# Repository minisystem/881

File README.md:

SYSTEM80 881
======================================

Trigger expander module for 880

Hardware design by Minisystem: info@system80.net

LICENSE
=======
cc by-nc-sa
https://creativecommons.org/licenses/by-nc-sa/4.0/

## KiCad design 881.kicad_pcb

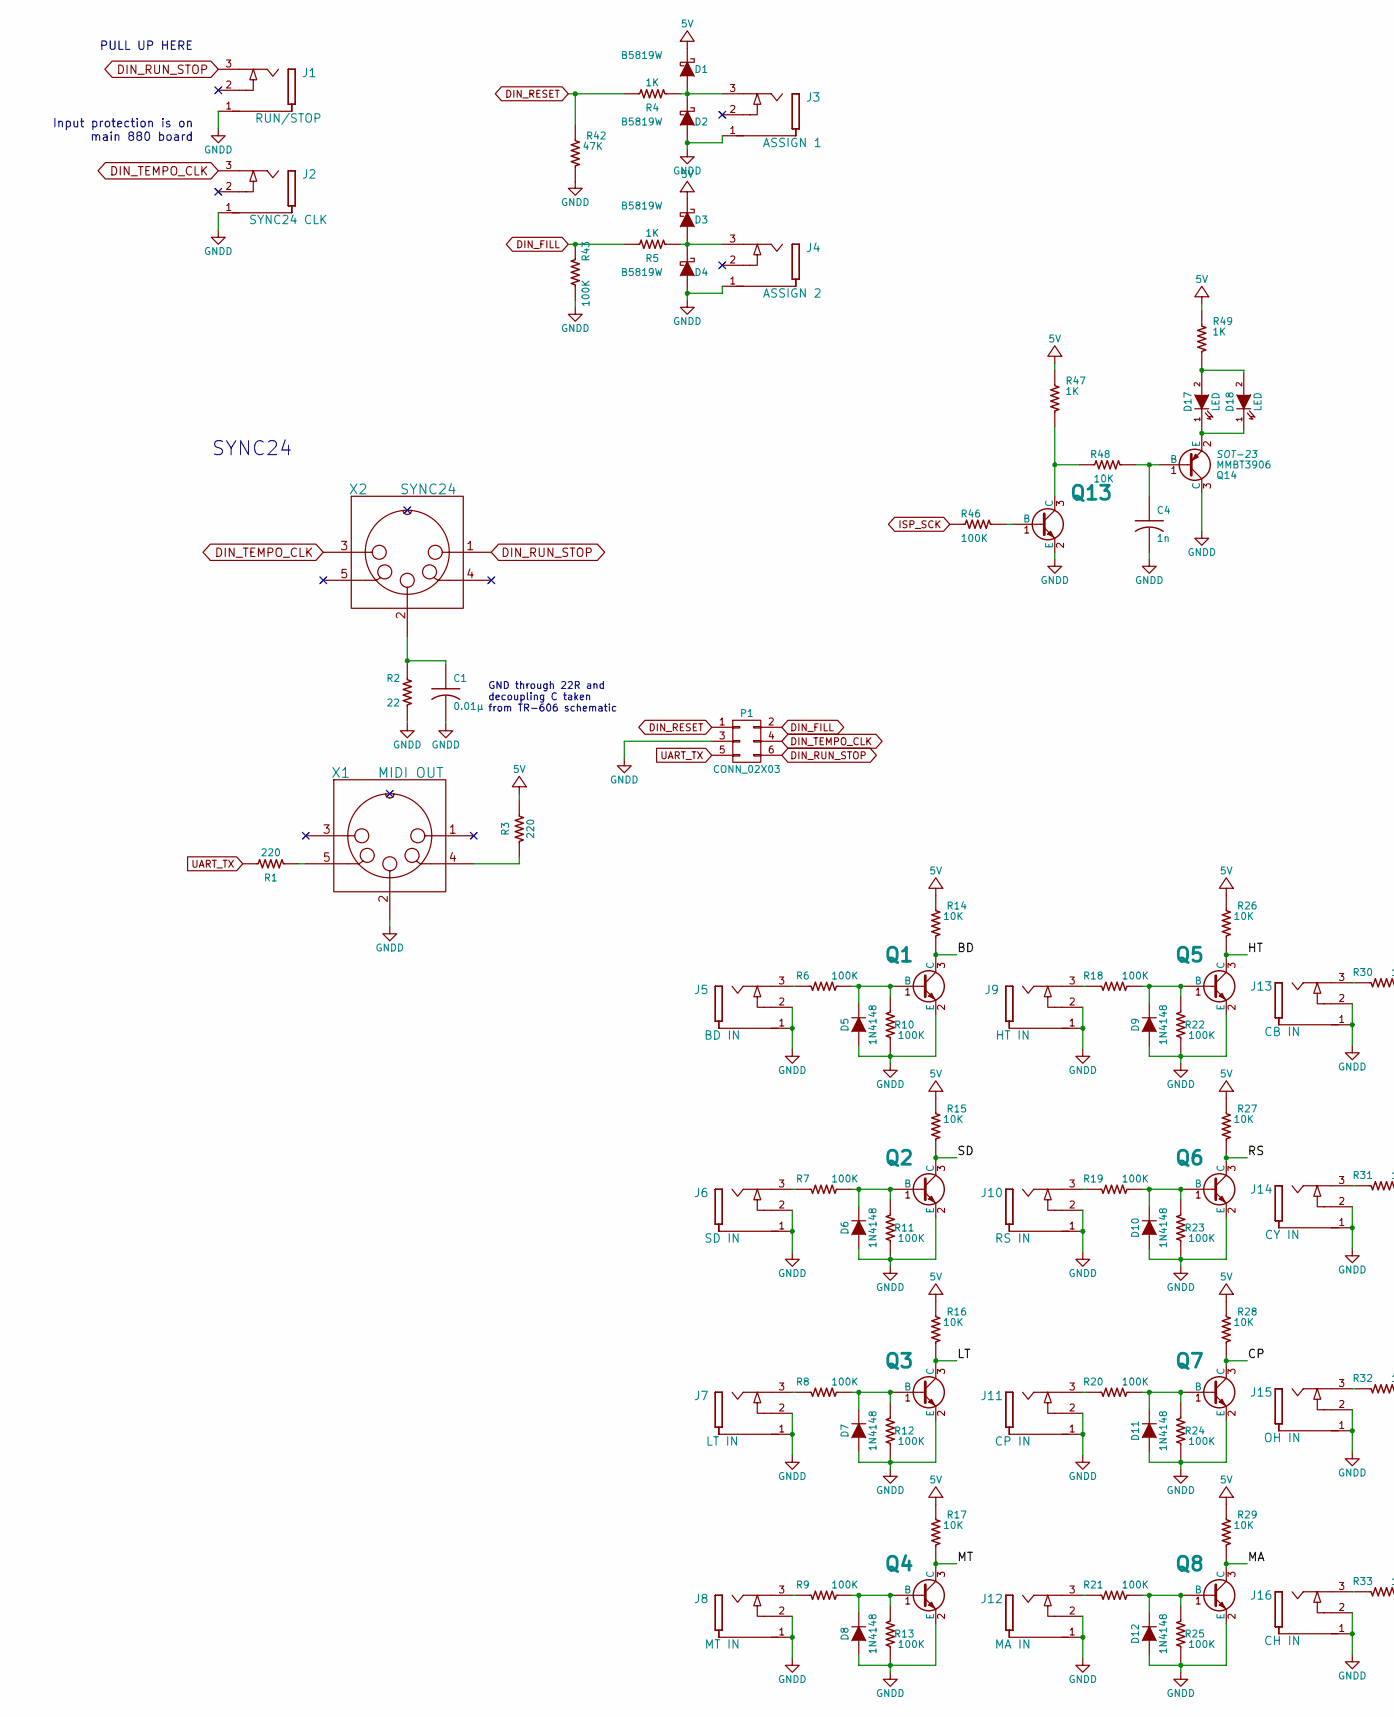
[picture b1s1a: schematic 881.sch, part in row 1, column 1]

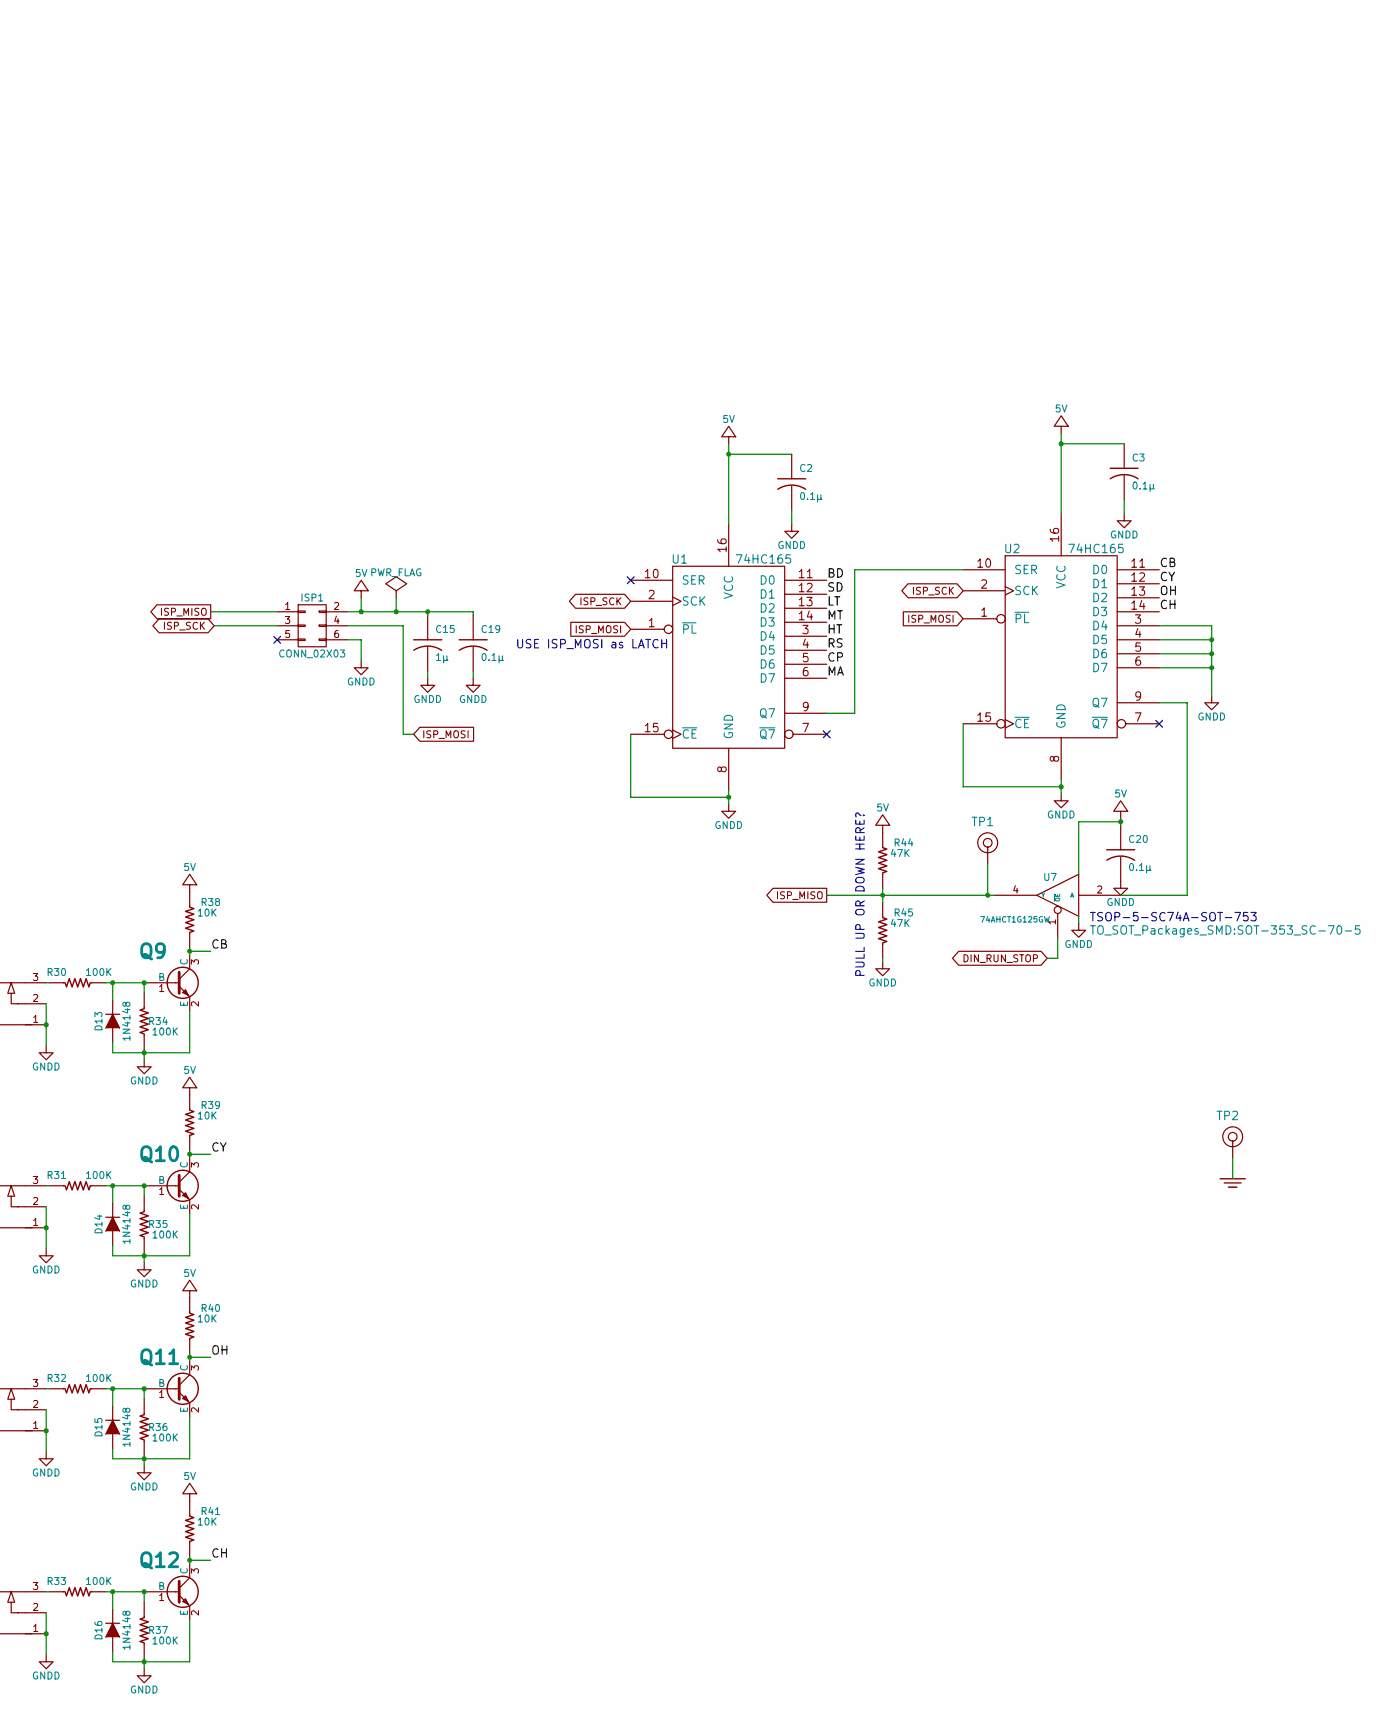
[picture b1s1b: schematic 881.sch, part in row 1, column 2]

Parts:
C1: 0.01µ; SM0603-C-MURATA
C2, C3, C19, C20: 0.1µ; SM0603-C-MURATA
C4: 1n; SM0603-C-MURATA
C15: 1µ; C_0805
D1: B5819W; D_SOD-123; JLC C8598
D2, D3, D4: B5819W; D_SOD-123
D5: 1N4148; D_SOD-323F; JLC C2128
D6, D7, D8, D9, D10, D11, D12, D13, D14, D15, D16: 1N4148; SOD323-C1A2
D17: LED; LED_0805; JLC C84256
D18: LED; LED_D3.0mm
ISP1: CONN_02X03; vasch_strip_3x2
J1: RUN/STOP; PJ-301B-JACK-SLOTS
J2: SYNC24 CLK; PJ-301B-JACK-SLOTS
J3: ASSIGN 1; PJ-301B-JACK-SLOTS
J4: ASSIGN 2; PJ-301B-JACK-SLOTS
J5: BD IN; PJ-301B-JACK-SLOTS
J6: SD IN; PJ-301B-JACK-SLOTS
J7: LT IN; PJ-301B-JACK-SLOTS
J8: MT IN; PJ-301B-JACK-SLOTS
J9: HT IN; PJ-301B-JACK-SLOTS
J10: RS IN; PJ-301B-JACK-SLOTS
J11: CP IN; PJ-301B-JACK-SLOTS
J12: MA IN; PJ-301B-JACK-SLOTS
J13: CB IN; PJ-301B-JACK-SLOTS
J14: CY IN; PJ-301B-JACK-SLOTS
J15: OH IN; PJ-301B-JACK-SLOTS
J16: CH IN; PJ-301B-JACK-SLOTS
P1: CONN_02X03; vasch_strip_4x2
Q1, Q2, Q3, Q4, Q5, Q6, Q7, Q8, Q9, Q10, Q11, Q12, Q13: MMBT3904; SOT23-132-JRL
Q14: MMBT3906; SOT-23
R1, R3: 220; SM0603-R-YAGEO
R2: 22; SM0603-R-YAGEO
R4, R5, R47, R49: 1K; SM0603-R-YAGEO
R6, R7, R8, R9, R10, R11, R12, R13, R18, R19, R20, R21, R22, R23, R24, R25, R30, R31, R32, R33, R34, R35, R36, R37, R43, R46: 100K; SM0603-R-YAGEO
R14, R15, R16, R17, R26, R27, R28, R29, R38, R39, R40, R41, R48: 10K; SM0603-R-YAGEO
R42, R44, R45: 47K; SM0603-R-YAGEO
TP1, TP2: CONN_1; TEST_POINT_LOOP_4592
U1, U2: 74HC165; SOIC-16_3.9x9.9mm_Pitch1.27mm; JLC C5613
U7: 74AHCT1G125GW; SOT-353_SC-70-5; JLC C12495
X1: MIDI OUT; SD-50BV-5DIN
X2: SYNC24; SD-50BV-5DIN

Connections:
+5V: C2.1, C3.1, C15.1, C19.1, C20.1, D1.1 (K), D3.1 (K), ISP1.2, R3.2, R14.1, R15.1, R16.1, R17.1, R26.1, R27.1, R28.1, R29.1, R38.1, R39.1, R40.1, R41.1, R44.1, R47.1, R49.1, U1.16 (VCC), U2.16 (VCC), U7.5 (VCC)
/BD: Q1.3 (C), R14.2, U1.11 (D0)
/CB: Q9.3 (C), R38.2, U2.11 (D0)
/CH: Q12.3 (C), R41.2, U2.14 (D3)
/CP: Q7.3 (C), R28.2, U1.5 (D6)
/CY: Q10.3 (C), R39.2, U2.12 (D1)
/HT: Q5.3 (C), R26.2, U1.3 (D4)
/LT: Q3.3 (C), R16.2, U1.13 (D2)
/MA: Q8.3 (C), R29.2, U1.6 (D7)
/MT: Q4.3 (C), R17.2, U1.14 (D3)
/OH: Q11.3 (C), R40.2, U2.13 (D2)
/RS: Q6.3 (C), R27.2, U1.4 (D5)
/SD: Q2.3 (C), R15.2, U1.12 (D1)
DIN_FILL: P1.2, R5.2, R43.1
DIN_RESET: P1.1, R4.2, R42.1
DIN_RUN_STOP: J1.3, P1.6, U7.1 (~OE), X2.1
DIN_TEMPO_CLK: J2.3, P1.4, X2.3
GNDD: C1.2, C2.2, C3.2, C4.2, C15.2, C19.2, C20.2, D2.2 (A), D4.2 (A), D5.2 (A), D6.2 (A), D7.2 (A), D8.2 (A), D9.2 (A), D10.2 (A), D11.2 (A), D12.2 (A), D13.2 (A), D14.2 (A), D15.2 (A), D16.2 (A), ISP1.6, J1.1, J2.1, J3.1, J4.1, J5.1, J5.2, J6.1, J6.2, J7.1, J7.2, J8.1, J8.2, J9.1, J9.2, J10.1, J10.2, J11.1, J11.2, J12.1, J12.2, J13.1, J13.2, J14.1, J14.2, J15.1, J15.2, J16.1, J16.2, P1.3, Q1.2 (E), Q2.2 (E), Q3.2 (E), Q4.2 (E), Q5.2 (E), Q6.2 (E), Q7.2 (E), Q8.2 (E), Q9.2 (E), Q10.2 (E), Q11.2 (E), Q12.2 (E), Q13.2 (E), Q14.3 (C), R2.1, R10.2, R11.2, R12.2, R13.2, R22.2, R23.2, R24.2, R25.2, R34.2, R35.2, R36.2, R37.2, R42.2, R43.2, R45.2, U1.8 (GND), U1.15 (~CE), U2.3 (D4), U2.4 (D5), U2.5 (D6), U2.6 (D7), U2.8 (GND), U2.15 (~CE), U7.3 (GNDD), X1.2
ISP_MISO: ISP1.1, R44.2, R45.1, TP1.1, U7.4 (Y)
ISP_MOSI: ISP1.4, U1.1 (~PL), U2.1 (~PL)
ISP_SCK: ISP1.3, R46.2, U1.2 (SCK), U2.2 (SCK)
unnamed: C1.1, R2.2, X2.2
unnamed: D1.2 (A), D2.1 (K), J3.3, R4.1
unnamed: D3.2 (A), D4.1 (K), J4.3, R5.1
unnamed: D5.1 (K), Q1.1 (B), R6.2, R10.1
unnamed: D6.1 (K), Q2.1 (B), R7.2, R11.1
unnamed: D7.1 (K), Q3.1 (B), R8.2, R12.1
unnamed: D8.1 (K), Q4.1 (B), R9.2, R13.1
unnamed: D9.1 (K), Q5.1 (B), R18.2, R22.1
unnamed: D10.1 (K), Q6.1 (B), R19.2, R23.1
unnamed: D11.1 (K), Q7.1 (B), R20.2, R24.1
unnamed: D12.1 (K), Q8.1 (B), R21.2, R25.1
unnamed: D13.1 (K), Q9.1 (B), R30.2, R34.1
unnamed: D14.1 (K), Q10.1 (B), R31.2, R35.1
unnamed: D15.1 (K), Q11.1 (B), R32.2, R36.1
unnamed: D16.1 (K), Q12.1 (B), R33.2, R37.1
unnamed: D17.1 (K), D18.1 (K), Q14.2 (E)
unnamed: D17.2 (A), D18.2 (A), R49.2
unnamed: J5.3, R6.1
unnamed: J6.3, R7.1
unnamed: J7.3, R8.1
unnamed: J8.3, R9.1
unnamed: J9.3, R18.1
unnamed: J10.3, R19.1
unnamed: J11.3, R20.1
unnamed: J12.3, R21.1
unnamed: J13.3, R30.1
unnamed: J14.3, R31.1
unnamed: J15.3, R32.1
unnamed: J16.3, R33.1
unnamed: Q13.3 (C), R47.2, R48.2
unnamed: R1.1, X1.5
unnamed: R3.1, X1.4
unnamed: U1.9 (Q7), U2.10 (SER)
unnamed: U2.9 (Q7), U7.2 (A)
UART_TX: P1.5, R1.2

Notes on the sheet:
SYNC24
GND through 22R and decoupling C taken from TR-606 schematic
USE ISP_MOSI as LATCH
Input protection is on main 880 board
TSOP-5-SC74A-SOT-753
PULL UP OR DOWN HERE?
PULL UP HERE

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
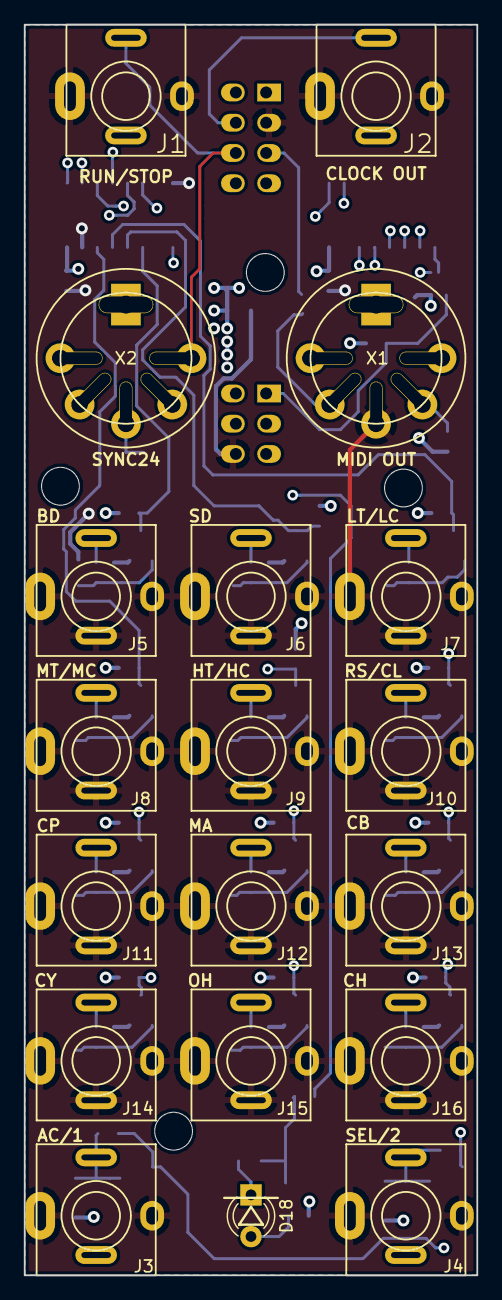
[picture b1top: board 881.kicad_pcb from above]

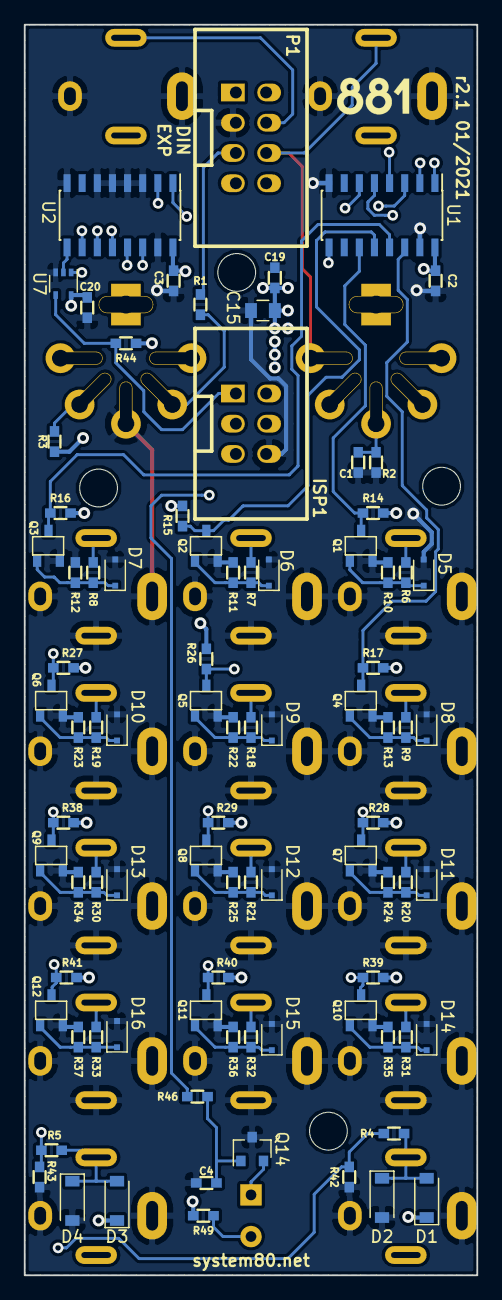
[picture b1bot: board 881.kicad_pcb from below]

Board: 4 copper layers, 38.0 x 105.0 mm, 110 parts (87 on the bottom side), 56 nets.

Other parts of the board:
SNAP-HOLE-0.125-INCH, SNAP-HOLE-0.125-INCH#2, SNAP-HOLE-0.125-INCH#3, SNAP-HOLE-0.125-INCH#4: VAL**; SNAP_HOLE_0.125_INCH

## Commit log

2018-09-23 schematic captured, started layout
2018-09-23 placed and routed
2018-09-24 ground stitching, tweaking
2018-10-03 first prototype PCB ordered
2018-11-05 notes added, going to turn this into trigger-MIDI converter
2020-09-25 first version of 881, obsolete. next commit will begin with new version for connection to 880 TII and DIN EXP
2020-09-26 schematic and footprint almost complete. spi clock or run-stop line for TII active indication still debatable, but leaning towards SPI SCK for LED indication
2020-09-27 first route
2020-09-28 routed with more finesse
2020-09-28 routed, finessed, ready to order me thinks
2020-09-29 DIN connector had wrong footprint. fixed. need to generate gerbers again before ordering
2024-04-17 2024 update with panel
2024-04-22 sent for quoting
